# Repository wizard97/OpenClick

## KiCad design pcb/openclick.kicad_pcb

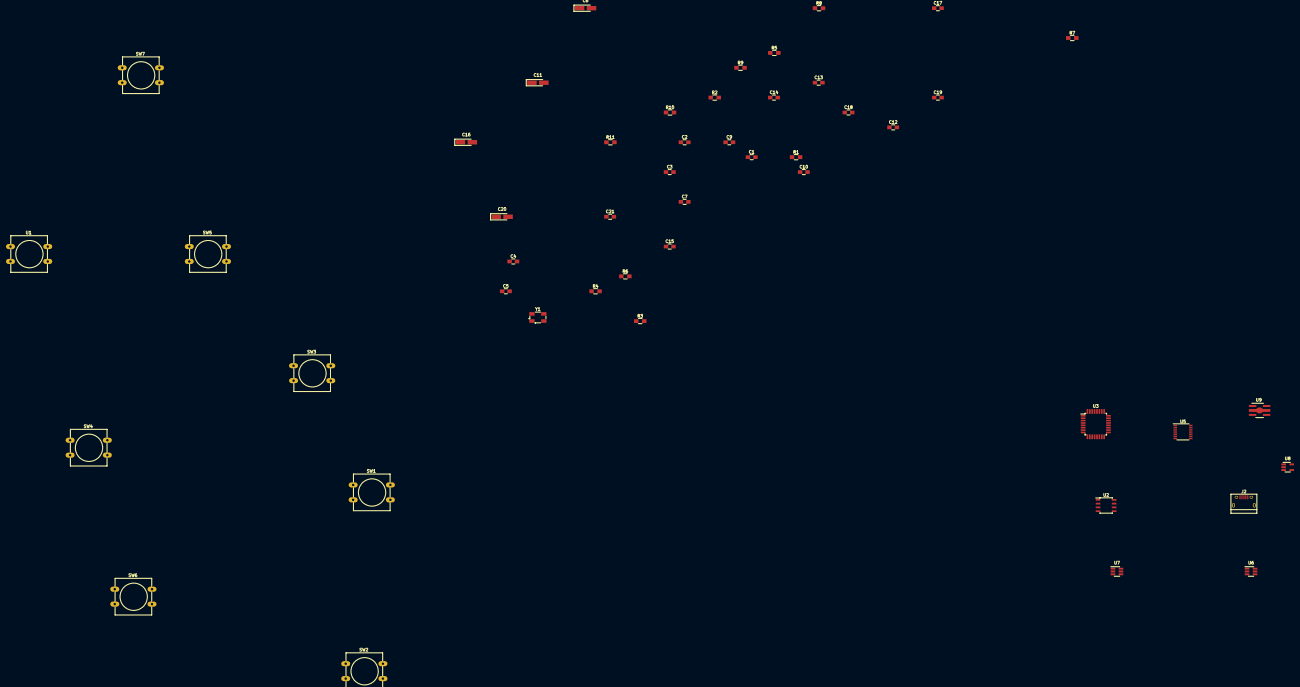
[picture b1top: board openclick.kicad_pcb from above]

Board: 2 copper layers, 48 parts (0 on the bottom side), 33 nets, no tracks yet.

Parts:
C1, C2, C3, C7, C9, C10, C12, C13, C14, C15, C17, C18, C19, C21: 0.1uF; C_0805_HandSoldering
C4, C5: 27pF; C_0805_HandSoldering
C6, C11, C16, C20: 10uF; CP_Tantalum_Case-A_EIA-3216-18_Hand
J2: USB_OTG; USB_Micro-B
R1, R2, R4, R5, R6, R7, R9: 10K; R_0805_HandSoldering
R3: 220; R_0805_HandSoldering
R8: 1M; R_0805_HandSoldering
R10: 430K; R_0805_HandSoldering
R11: 100k; R_0805_HandSoldering
SW1, SW2, SW3, SW4, SW5, SW6, SW7: SW_Push; SW_PUSH-12mm
U1: LCDSSD1306; SW_PUSH-12mm
U2: MB85RS64V; SOIC-8_3.9x4.9mm_Pitch1.27mm
U3: ATMEGA328P-AU; TQFP-32_7x7mm_Pitch0.8mm
U5: FT230X; SSOP-16_3.9x4.9mm_Pitch0.635mm
U6, U7: SN74LVC1T45DBVR; SOT-23-6_Handsoldering
U8: MC78LC33NTRG; SOT-23-5_HandSoldering
U9: XC6227C331PR-G; SOT-89-5_Housing_Handsoldering
Y1: ABM3B-8; Crystal_SMD_Abracon_ABM3B-4pin_5.0x3.2mm

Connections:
3V3_HP: C1.1, C6.1, C7.1, C19.1, C20.1, U1.1, U9.5
3V3_LP: C2.1, C3.1, C13.1, C15.1, R1.1, U2.3, U2.7, U2.8, U3.4, U3.6, U3.18, U3.20, U6.6, U7.6, U8.3
+BATT: C14.1, C16.1, C17.1, C18.1, R5.1, R6.1, R7.1, R10.1, U8.2, U9.4
/3V3_EN: R2.2, R9.1, U3.12, U9.1
/BATT_VOLT: C21.1, R10.2, R11.1, U3.23
/BTN_BACK: SW1.1, U3.24
/BTN_DWN: SW3.1, U3.26
/BTN_LEFT: SW2.1, U3.25
/BTN_MID: SW7.2, U3.10
/BTN_PWR: R1.2, SW4.2, U3.1
/BTN_RIGHT: SW6.2, U3.9
/BTN_UP: SW5.2, U3.2
/FRAM_CS: U2.1, U3.11
/MISO: R4.2, U2.2, U3.16
/MOSI: U2.5, U3.15
/SCK: U2.6, U3.17
/SCL: R6.2, U3.28
/SDA: R5.2, U3.27
/UC_RESET: C12.1, R7.2, U3.29
/UC_RX: U3.30, U7.3
/UC_TX: U3.31, U6.4
/USB_Serial/RX_IN: U5.4, U6.3
/USB_Serial/TX_OUT: U5.1, U7.4
/USB_Serial/UART_3V3: C9.1, U5.3, U5.10, U5.11, U6.1, U7.1
/USB_Serial/USB_5V: C10.1, C11.1, J2.1, U5.12
/USB_Serial/USB_D+: J2.3, U5.8
/USB_Serial/USB_D-: J2.2, U5.9
GND: C1.2, C2.2, C3.2, C4.2, C5.2, C6.2, C7.2, C9.2, C10.2, C11.2, C13.2, C14.2, C15.2, C16.2, C17.2, C18.2, C19.2, C20.2, C21.2, J2.5, R2.1, R4.1, R8.2, R9.2, R11.2, SW1.2, SW2.2, SW3.2, SW4.1, SW5.1, SW6.1, SW7.1, U1.2, U2.4, U3.3, U3.5, U3.21, U5.5, U5.13, U6.2, U6.5, U7.2, U7.5, U8.1, U9.2, Y1.2, Y1.4
unnamed: C4.1, U3.7, Y1.1
unnamed: C5.1, U3.8, Y1.3
unnamed: J2.6, R8.1
unnamed: C12.2, U5.2
unnamed: R3.1, U3.13

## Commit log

2019-01-17 Added pcb files
